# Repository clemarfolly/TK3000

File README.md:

# Microdigital TK-3000 IIe

A Microdigital Eletrônica Ltda foi uma das empresas pioneiras no mercado de microcomputadores no Brasil, tendo grande importância na popularização da informática durante a década de 1980. Fundada em 1979, a empresa se destacou por criar e distribuir uma série de microcomputadores compatíveis com modelos internacionais. A Microdigital se beneficiou da reserva de mercado imposta pelo governo brasileiro, o que levou a empresa a desenvolver produtos que atendessem à demanda interna por tecnologia, educação e entretenimento.

O TK-3000 IIe foi um computador pessoal brasileiro lançado em abril de 1986, inspirado no Apple IIe Enhanced, da Apple. Na época, ele chamou a atenção por oferecer boa compatibilidade com o sistema original, permitindo rodar diversos programas, jogos e ferramentas de programação. Equipado com processador de 1 MHz e 64 KB de memória RAM, o TK-3000 IIe também contava com recursos gráficos coloridos, teclado com acentuação em português e suporte a expansões e periféricos. Foi um dos computadores que marcaram a história da informática no Brasil durante os anos 1980, conquistando espaço entre usuários interessados em aprender programação, trabalhar e se divertir com a tecnologia da época.

## Sobre essa reprodução

A reprodução do projeto foi realizada sem acesso físico à placa original, com base em fotos da placa MA 104 sem componentes. Para isso, utilizou-se os software Sprint Layout e o KiCad para desenhar o esquema e a placa de circuito impresso. A réplica ainda não foi produzida, e seu funcionamento não foi validado. Agradecemos às pessoas que disponibilizaram as fotos e o esquema original, permitindo que esse trabalho fosse possível.

 ### Detalhes da placa
A placa é de dupla face e ficou com um tamanho final de 239 × 239 mm. Originalmente, os chips não têm uma identificação individual, sendo identificados apenas pela linha e coluna em que estão localizados. Para facilitar a montagem, adicionei o designador de cada circuito integrado diretamente na placa, dentro da área correspondente a ele.

### Comparação com a placa original
Como não tive acesso direto à placa original, fiz o que pude para que a recriação ficasse o mais fiel possível. Também recriei a fonte utilizada no projeto para deixar o resultado ainda mais parecido com o original.

O circuito de RF foi removido e, no lugar, foi adicionada uma saída de vídeo composto.

No TK-3000 original, a saída e a entrada de dados do cassete compartilham o mesmo circuito, o que pode causar incompatibilidades na leitura de dados a partir de algumas fontes de áudio. Para resolver esse problema, foi incluída uma entrada independente para leitura de dados, que pode ser ativada pelo jumper X6.

- Posição 1-2: mantém o funcionamento original do TK-3000.
- Posição 2-3: ativa a entrada independente de áudio para leitura de dados.

### Para confecção

Na seção de releases desta página, você encontrará todos os arquivos necessários para a fabricação da placa: o gerber em formato zip, o esquema em PDF e a lista interativa de materiais em HTML. Basta enviar o arquivo zip para a sua fabricante de PCB de preferência.

### Chips customizados

O TK-3000 possui três chips customizados: a MMU, a IOU e a GAL. Encontrar os chips originais MMU e IOU é bem difícil, mas é possível usar equivalentes do Apple IIe ou de clones asiáticos. Porém, é preciso ficar atento à disposição dos pinos, que pode ser diferente da original, exigindo o uso de adaptadores.

Outra alternativa mais moderna é utilizar versões desses chips recriadas em FPGA. Já a GAL é mais fácil de encontrar e está disponível para compra na internet.

As equações da GAL utilizadas no Apple IIe estão disponíveis na pasta PAL_G1 deste repositório e podem ser adaptadas para funcionar neste projeto.

## Créditos

### Recriação da Placa: 

Clemar Folly Jr.

https://x.com/clemarfolly/ - https://www.facebook.com/clemarjr

### Fotos 

Fotos da Placa sem componentes

William Barbacena, José Ferro

Post Facebook (indisponível no momento)

https://www.facebook.com/share/p/xtZCQikUJb32PADm/

Clube do TK - Logo Microdigital

http://www.tk90x.com.br/Download.html

Wikipedia

https://pt.wikipedia.org/wiki/Ficheiro:Microdigital_TK3000IIe_MoBo_MA104.jpg

### Esquema

Tabalabs - Esquema do TK 3000 e Diagrama de blocos

http://www.tabalabs.com.br/apple/esquemas_microdigital/index.htm

Esquemateca Tabalabs - Esquema do CCE Exato IIe

http://www.tabalabs.com.br/esquemateca/

### ROMs 

Datassette - Eduardo Luccas

https://datassette.org/pt-br/softwares/apple/apple-ii/firmwares/br-brasil/tk3000-roms-8kb

### Outras contribuições

Carlos Milek - Inclusão de alguns resistores, capacitores e transistor

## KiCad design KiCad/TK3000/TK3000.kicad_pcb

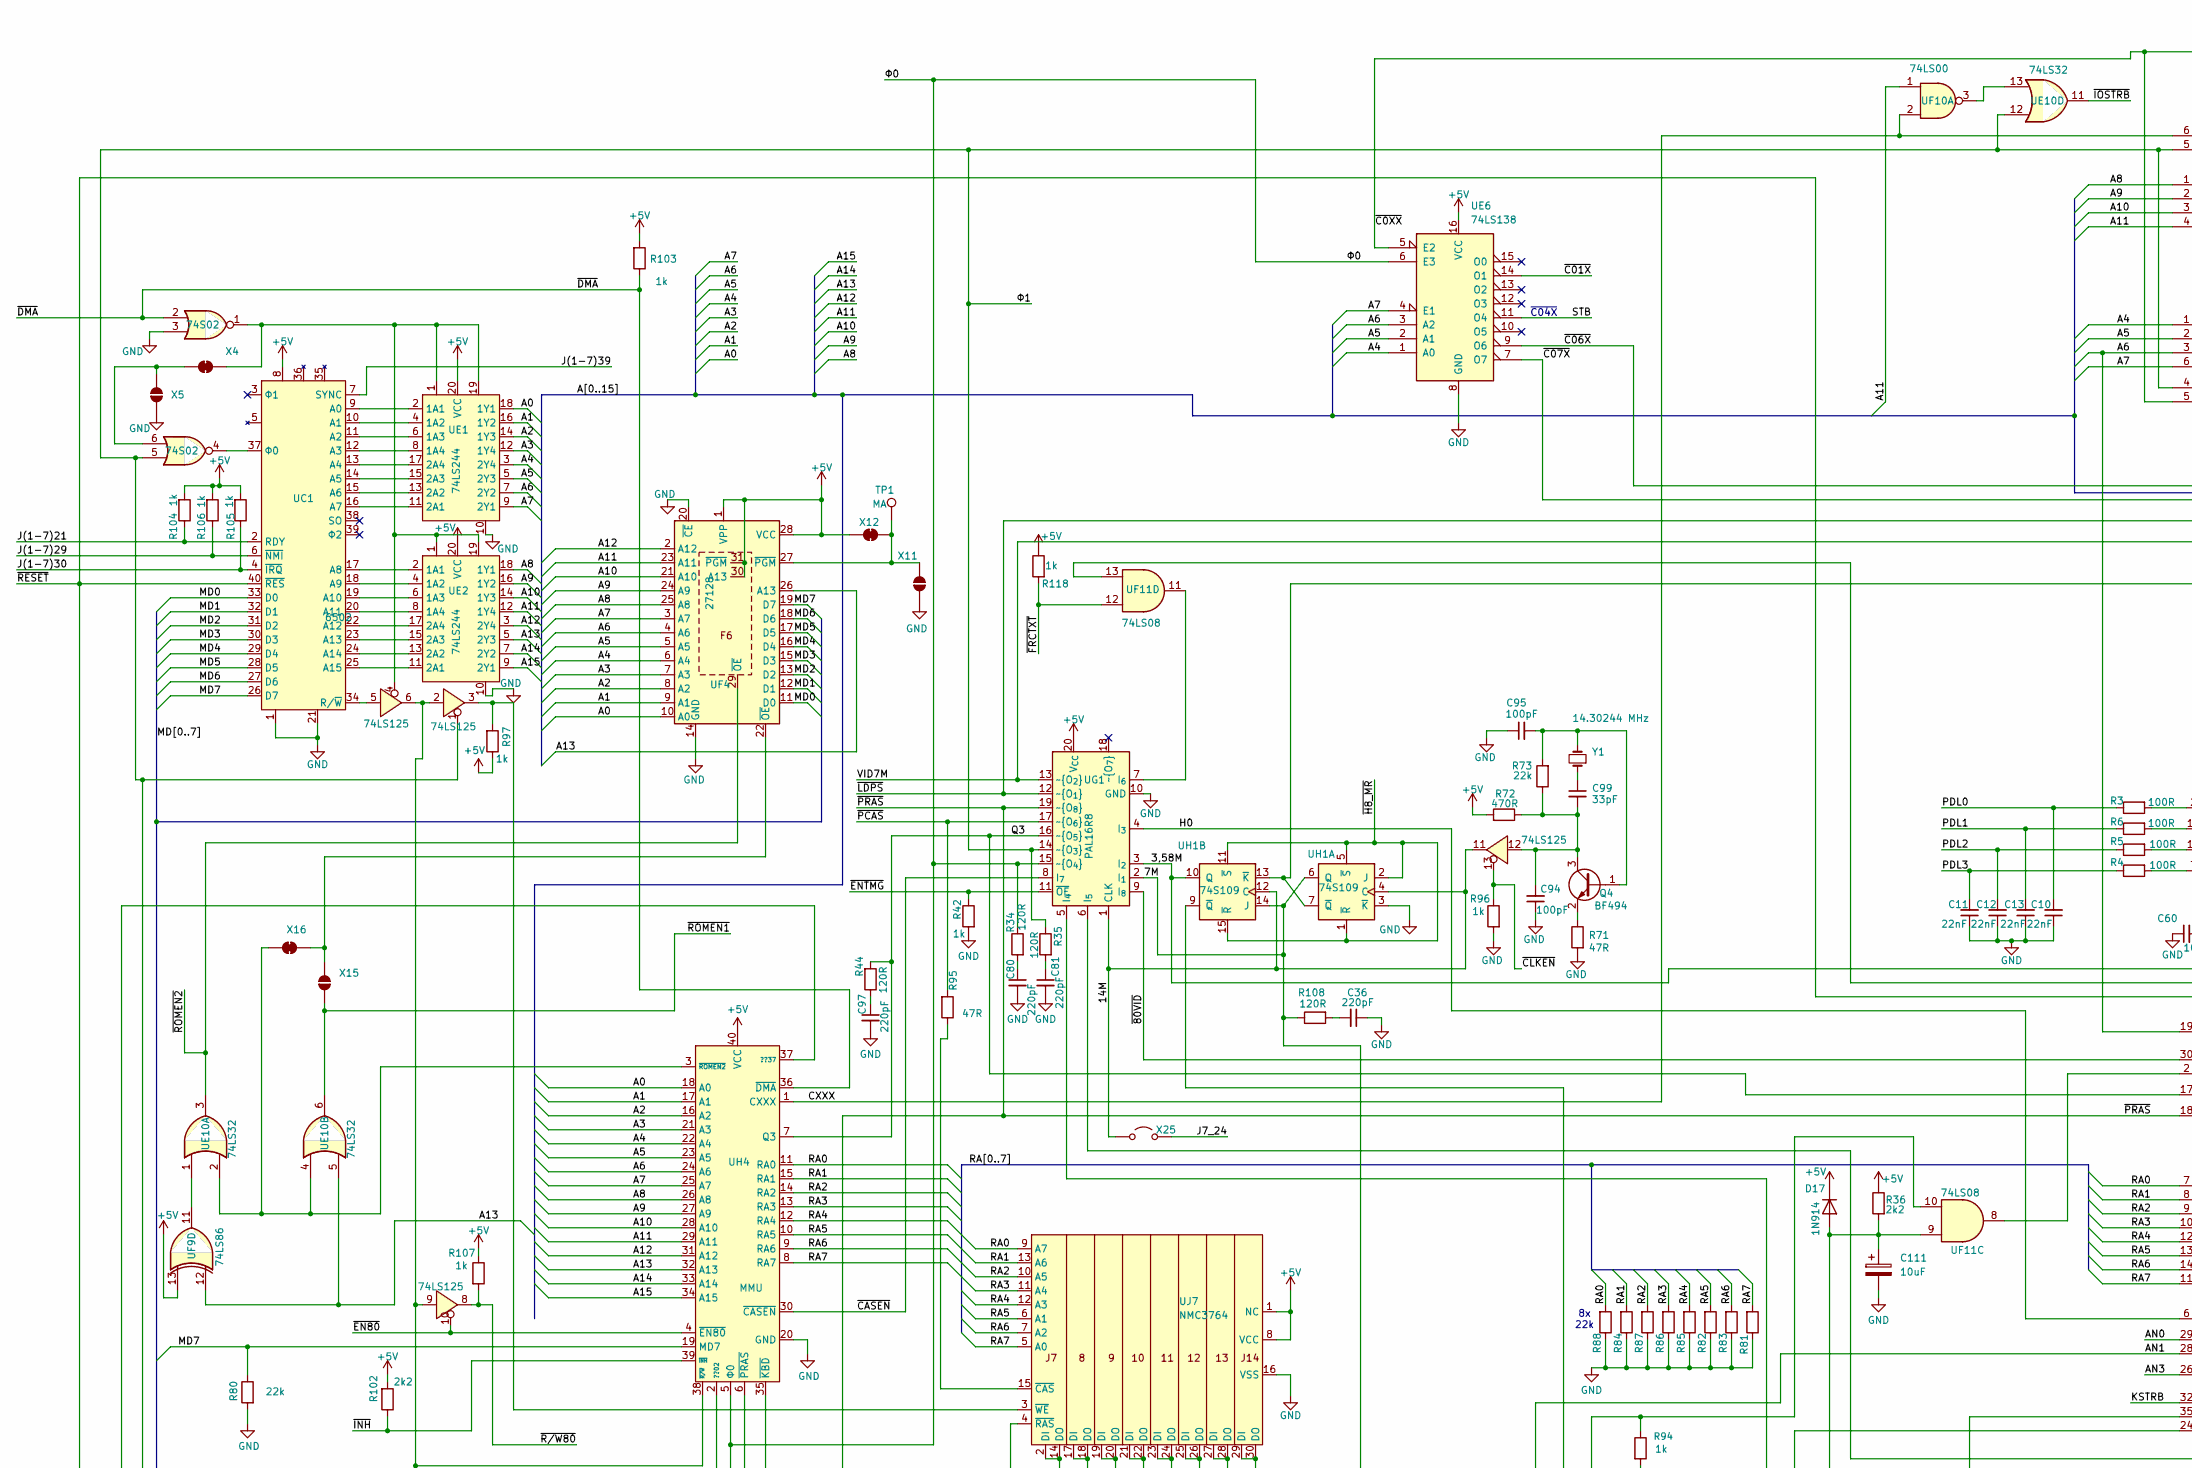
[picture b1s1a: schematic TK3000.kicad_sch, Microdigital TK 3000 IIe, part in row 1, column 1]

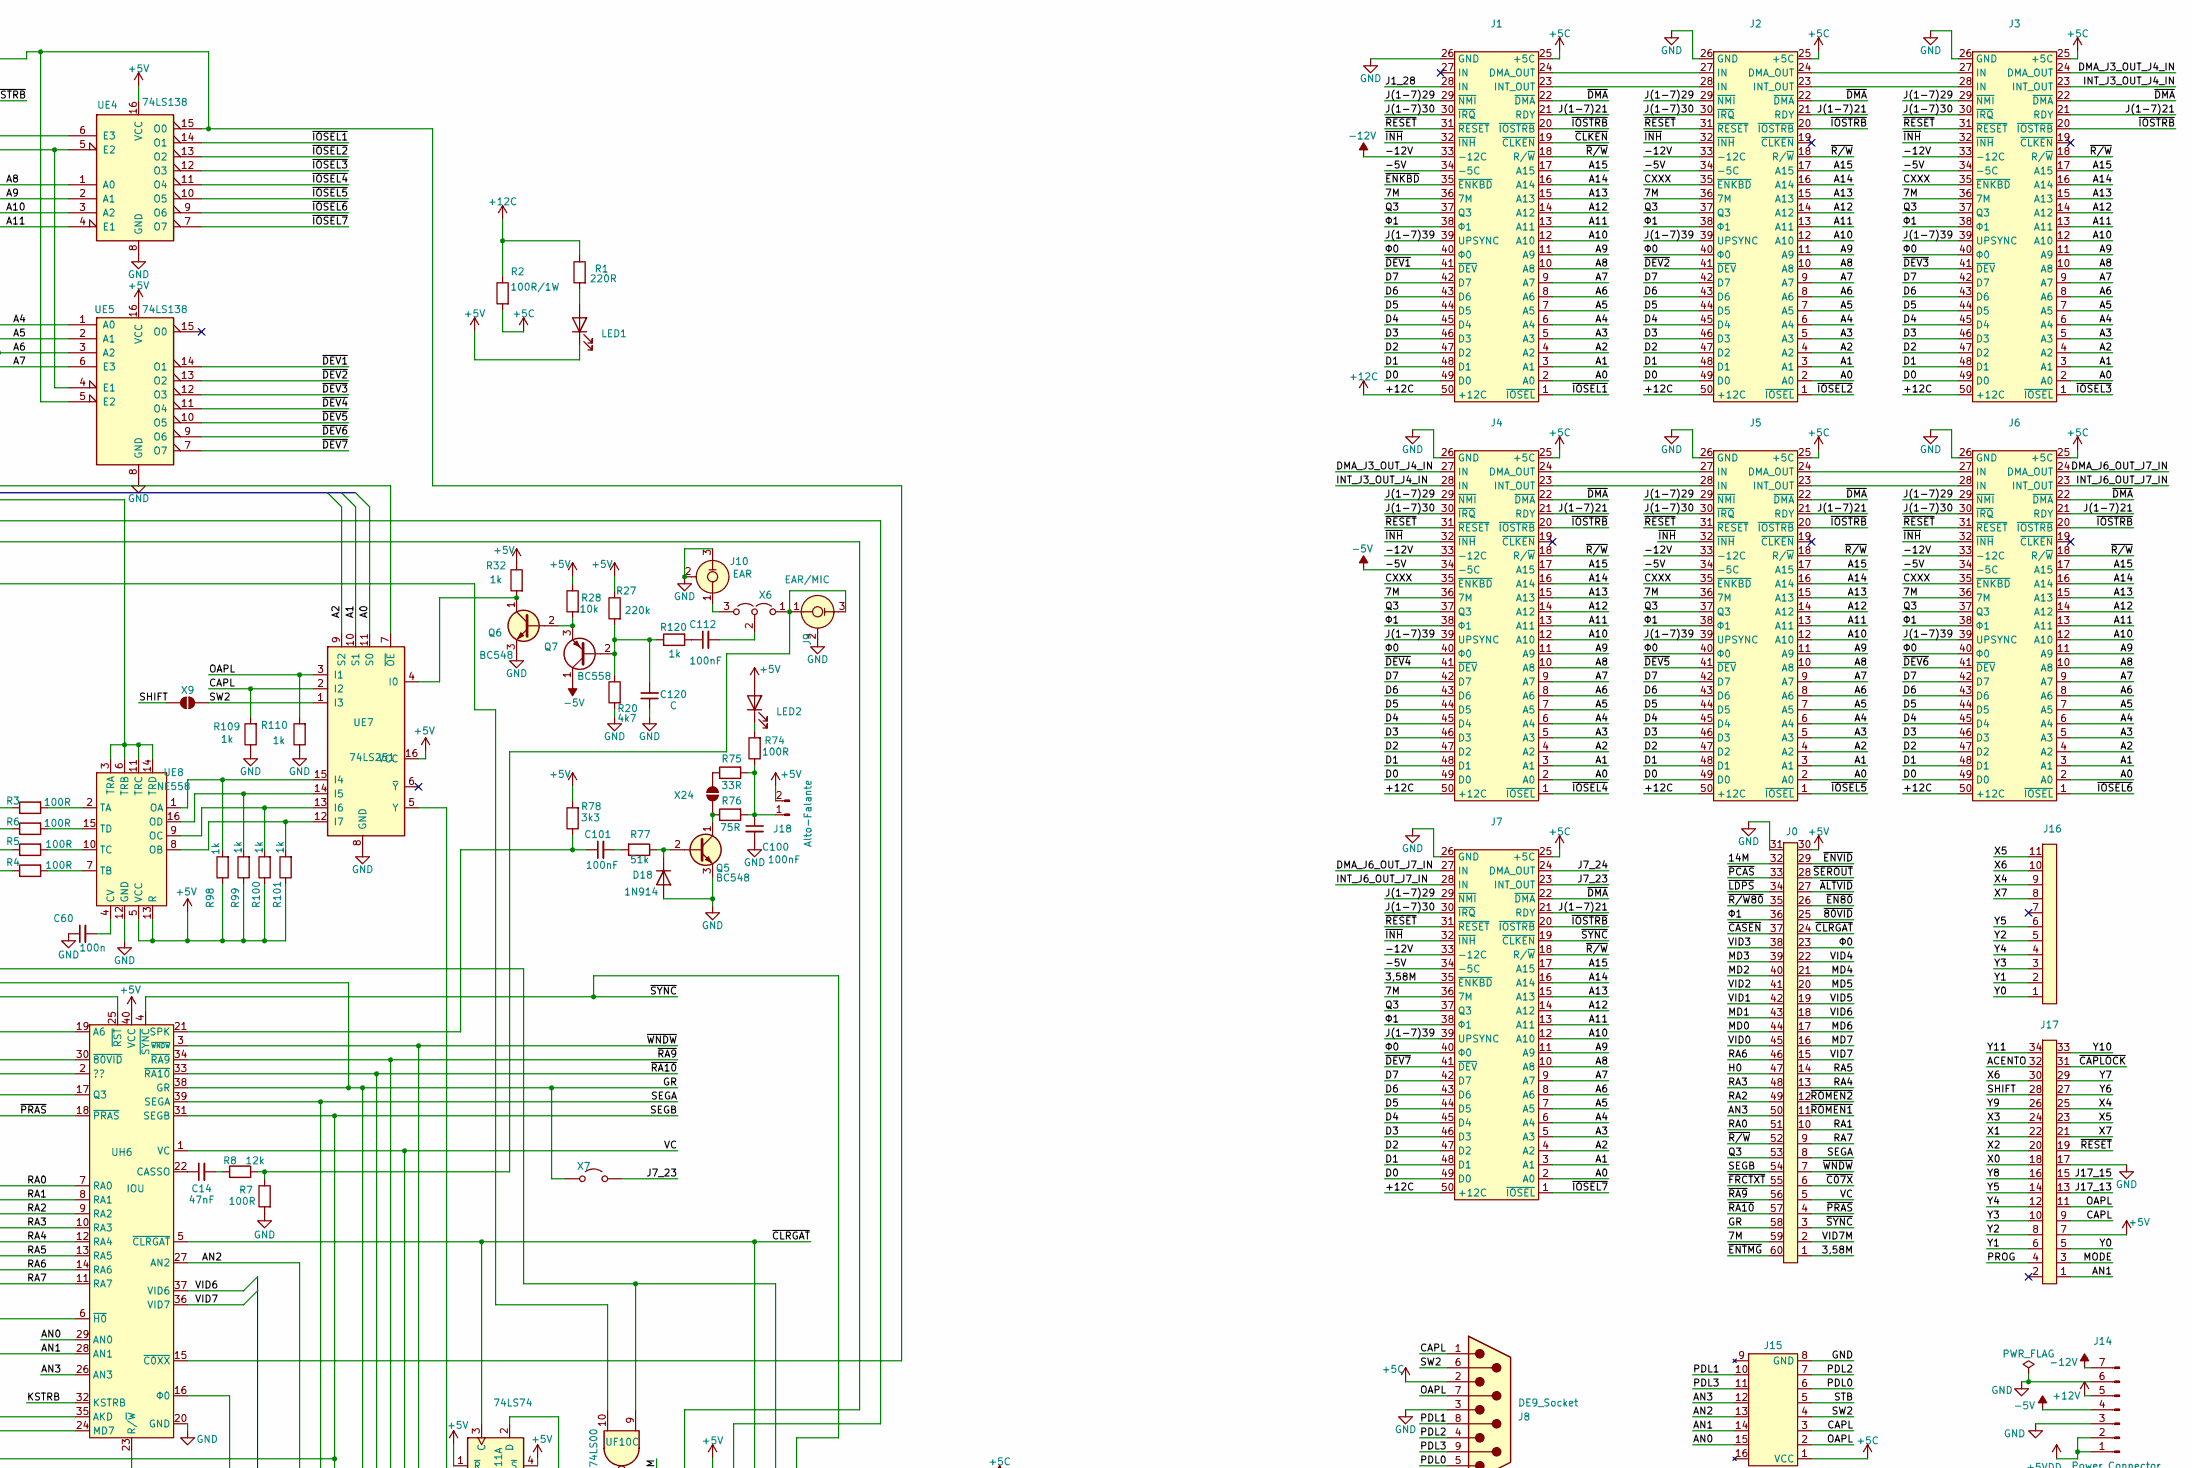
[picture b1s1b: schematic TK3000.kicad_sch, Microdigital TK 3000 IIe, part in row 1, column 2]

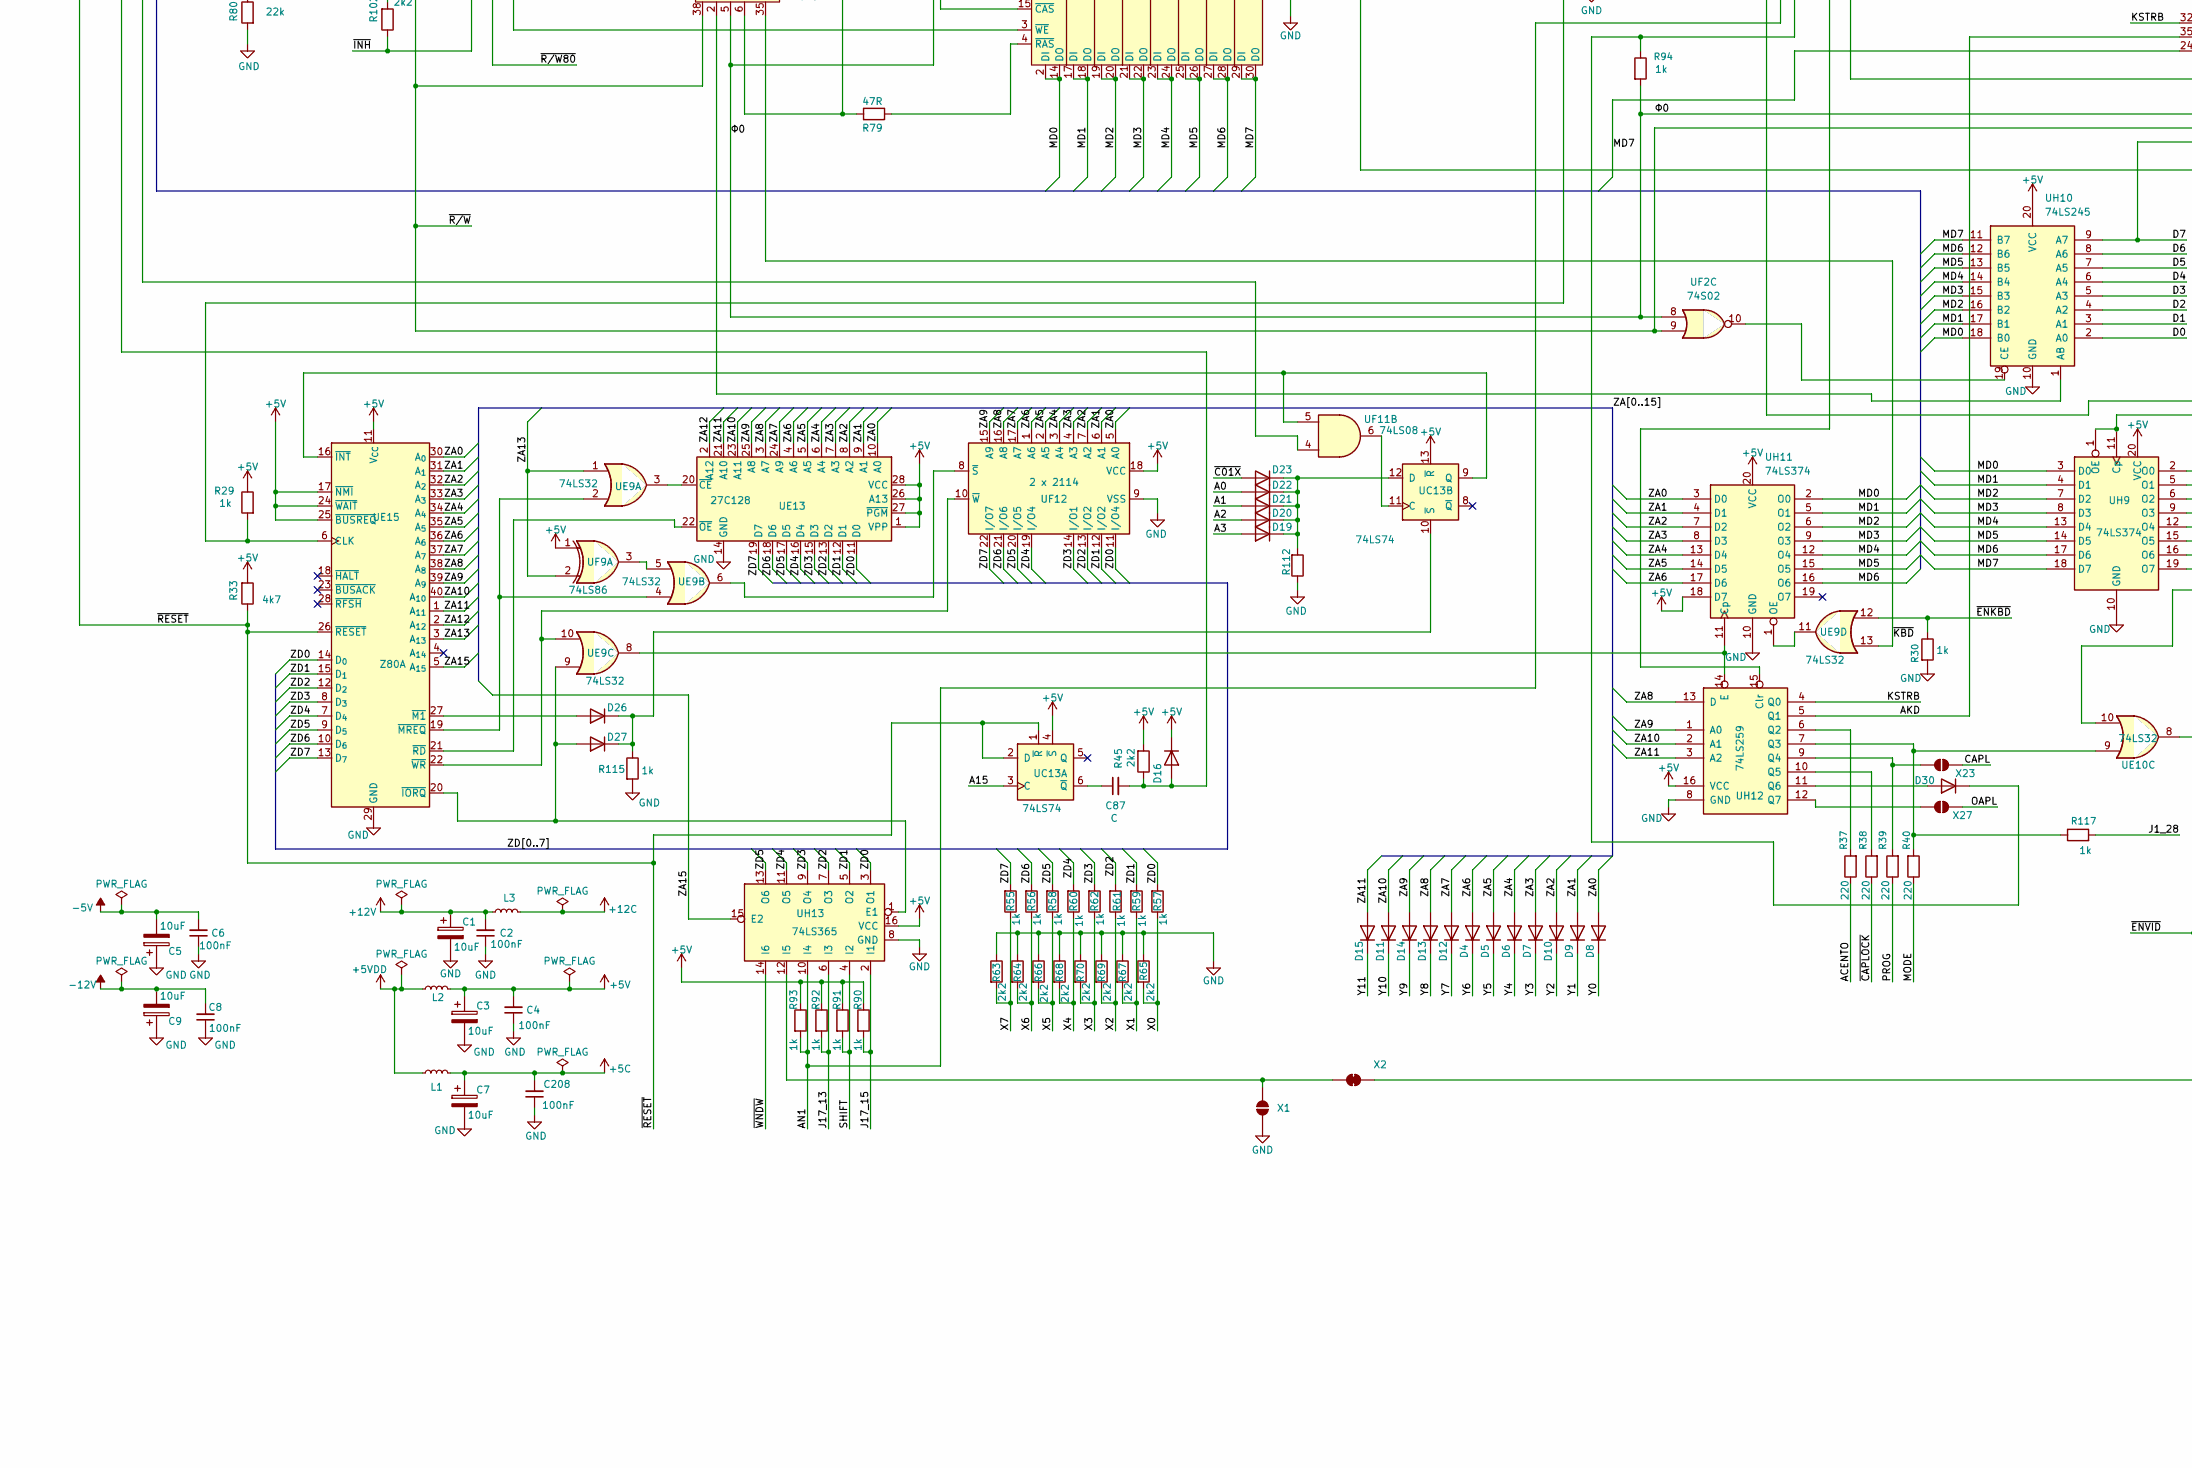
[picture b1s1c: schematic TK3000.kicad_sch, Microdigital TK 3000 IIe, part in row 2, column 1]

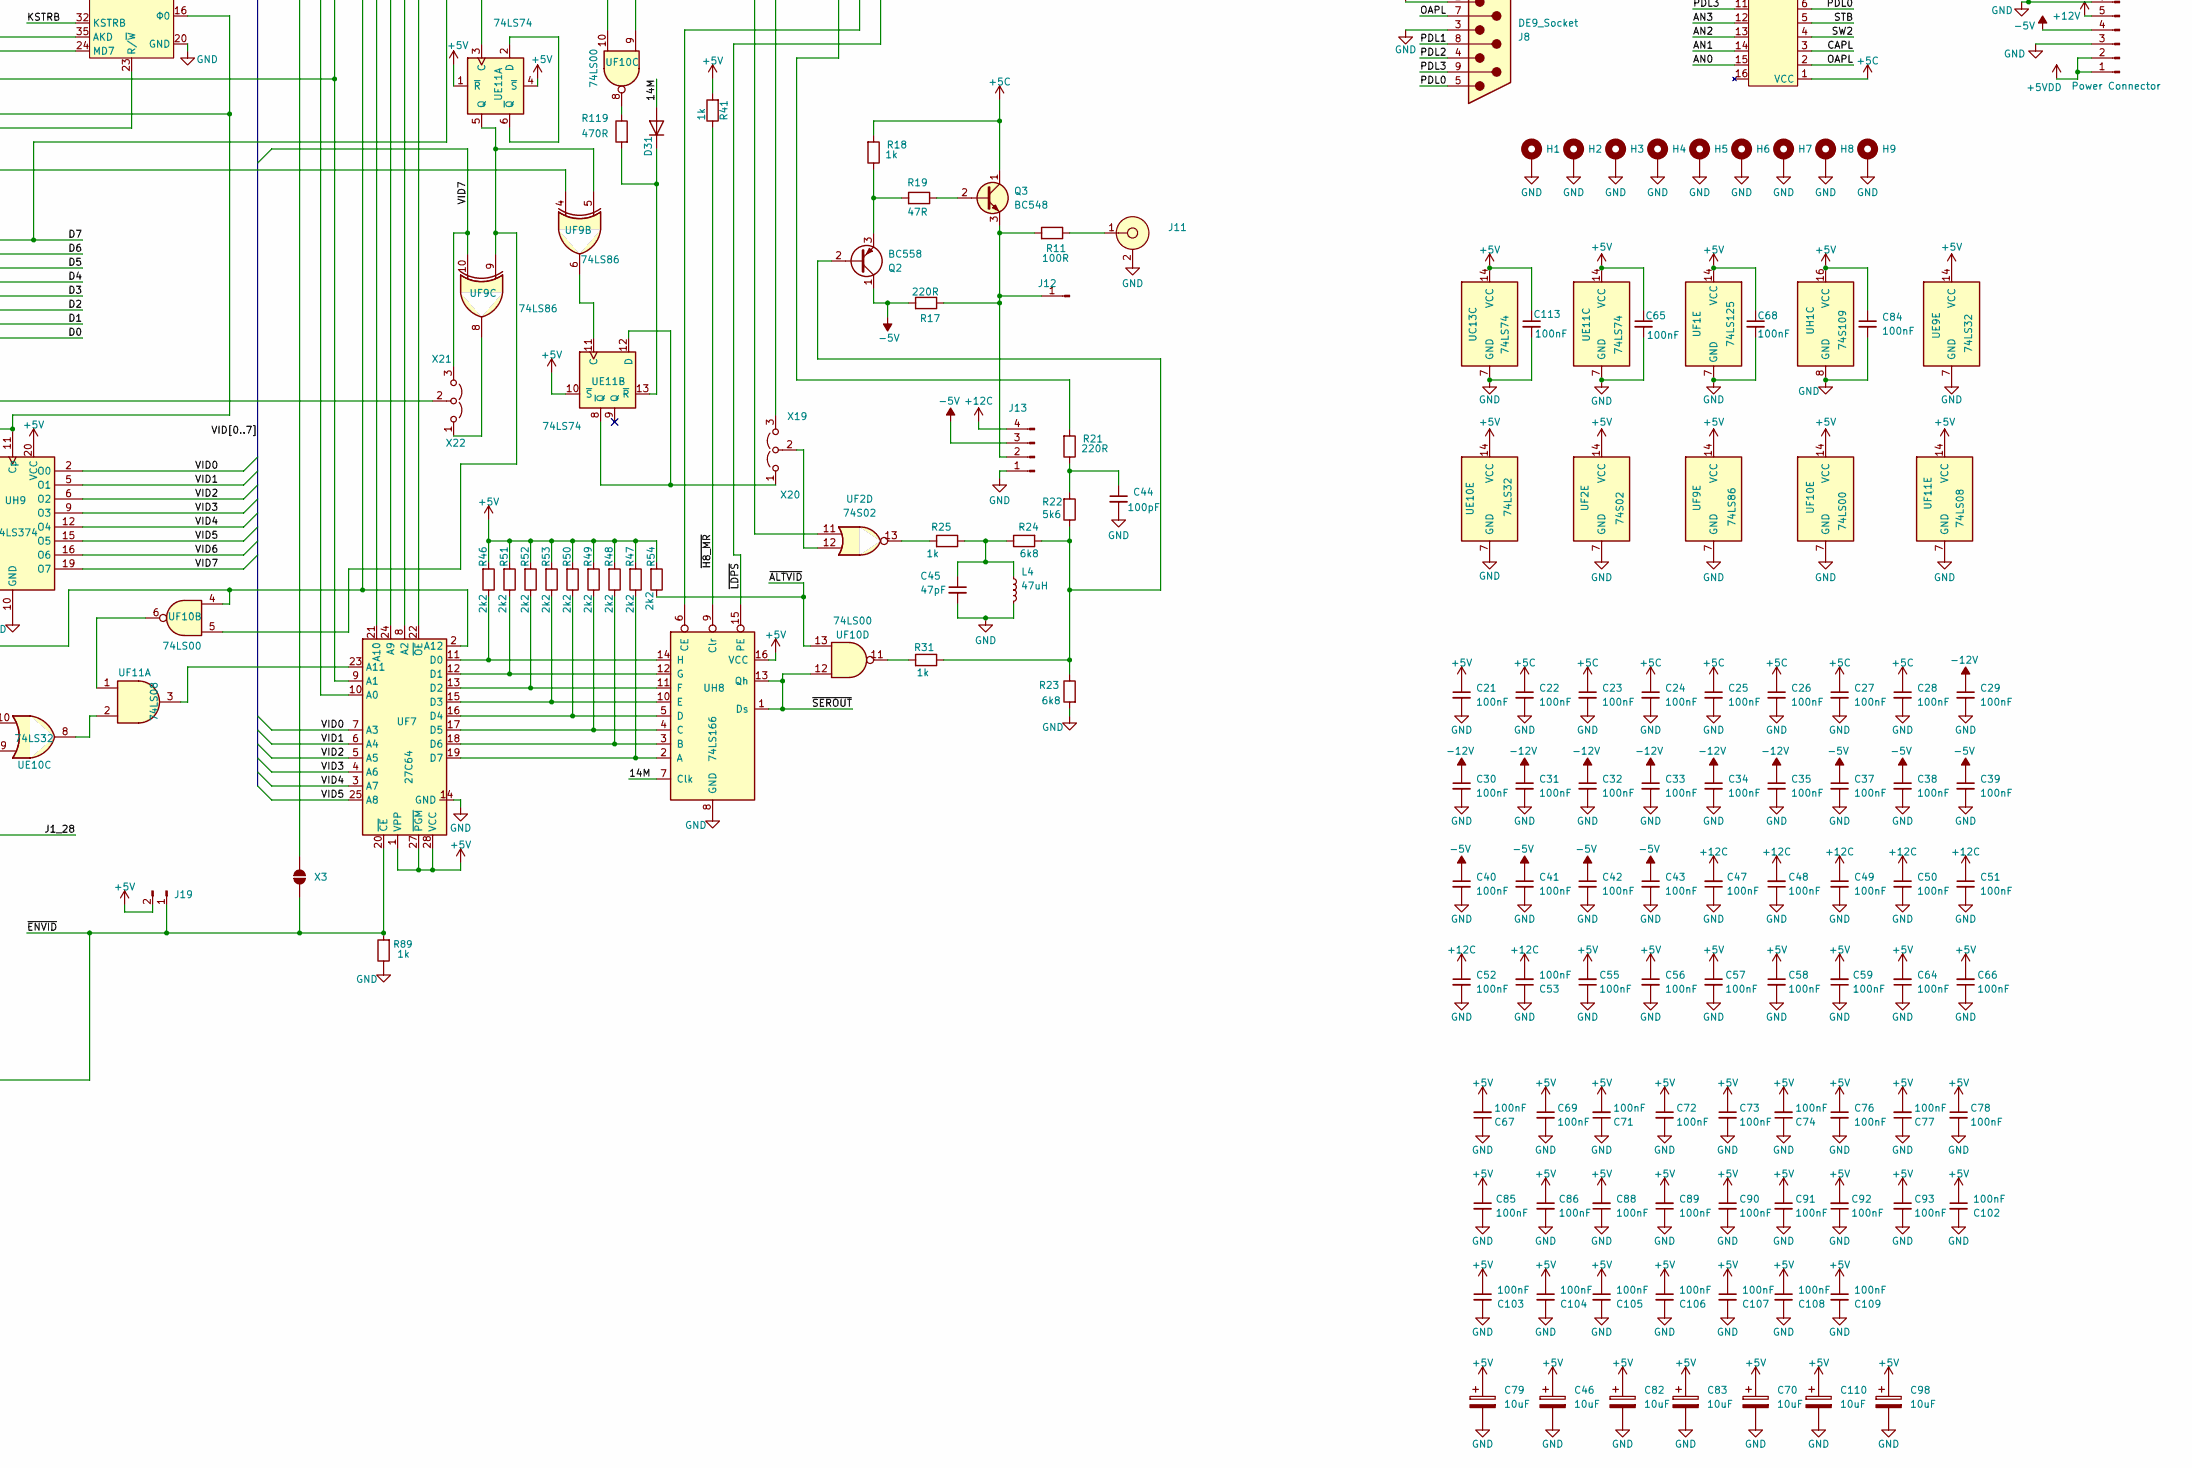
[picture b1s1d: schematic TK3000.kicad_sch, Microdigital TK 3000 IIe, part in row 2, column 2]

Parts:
C1, C3, C5, C9, C79, C82, C111: 10uF; C_Elet_111
C2, C4, C6, C8, C29, C30, C31, C32, C33, C34, C35, C57, C101, C112, C113, C208: 100nF; C_Disc_5.08
C7, C46, C70, C83: 10uF; C_Elet_Tipo2
C10, C11, C12, C13: 22nF; C_Disc_5.08
C14: 47nF; C_Disc_5.08
C21, C23, C24, C25, C26, C27, C28, C37, C38, C39, C40, C41, C42, C43, C47, C48, C49, C50, C51, C52, C53, C55, C58, C59, C64, C66, C67, C68, C69, C71, C72, C73, C74, C77, C78, C84, C86, C89, C90, C91, C92, C93, C102, C103, C104, C105, C106, C107, C108, C109: 100nF; C_Disc_5.08_12.7mm
C22, C56, C76, C85, C88: 100nF; C_Disc_12.7mm
C36, C80, C81, C97: 220pF; C_Disc_5.08
C44, C94, C95: 100pF; C_Disc_5.08
C45: 47pF; C_Disc_5.08
C60: 100n; C_Disc_5.08
C65: 100nF; C65_Disc_5.08_12.7mm
C87, C120: C; C_Disc_5.08
C98: 10uF; CP_Disc_5.08
C99: 33pF; C_Disc_5.08
C100: 100nF; C_Disc_C100
C110: 10uF; C_Elet_C110
D4, D5, D6, D7, D8, D9, D10, D11, D12, D13, D14, D15, D19, D20, D21, D22, D23, D30: 1N914; D_5.08
D16, D17, D26, D27, D31: 1N914; D_12.7
D18: 1N914; D_D18
H1, H9: MountingHole_Pad; Furo_8mm_5mm
H2, H3, H4: MountingHole_Pad; Furo_7mm_4mm
H5, H6, H7, H8: MountingHole_Pad; Furo_5mm_3mm
J0: SLOT-60_W5.08
J1, J2, J3, J4, J5, J6, J7: SLOT-50_W5.08
J8: DE9_Socket; DB9
J9: EAR/MIC; EarJack
J10: EAR; EarJack
J11: RCA_AV-8,4-5A
J12: Conn_01x01_Pin; J12
J13: J13
J14: Power Connector; J14
J15: GAME_IO
J16: J16
J17: J17
J18: Alto-Falante; J18
J19: Conn_01x02_Pin; PinHeader_1x02_P2.54mm_Vertical
L1, L2, L3: Ind
L4: 47uH; Ind_762
LED1: LED; led1
LED2: LED; led2
Q2, Q7: BC558
Q3, Q5, Q6: BC548
Q4: BF494
R1, R17, R21: 220R; Resistor_P12.70mm_Horizontal
R2: 100R/1W; Res_20.32
R3, R4, R5, R6, R7, R74: 100R; Resistor_P5.08mm_Vertical
R8: 12k; Resistor_P5.08mm_Vertical
R11: 100R; Resistor_P12.70mm_Horizontal
R18, R25, R29, R30, R31, R32, R89, R115, R117, R118, R120: 1k; Resistor_P12.70mm_Horizontal
R19: 47R; Resistor_P12.70mm_Horizontal
R20, R33: 4k7; Resistor_P12.70mm_Horizontal
R22: 5k6; Resistor_P12.70mm_Horizontal
R23, R24: 6k8; Resistor_P12.70mm_Horizontal
R27: 220k; Resistor_P12.70mm_Horizontal
R28: 10k; Resistor_P12.70mm_Horizontal
R34, R35, R44, R108: 120R; Resistor_P5.08mm_Vertical
R36, R45: 2k2; Resistor_P12.70mm_Horizontal
R37, R38, R39, R40: 220; Resistor_P5.08mm_Vertical
R41, R42, R55, R56, R57, R58, R59, R60, R61, R62, R90, R91, R92, R93, R94, R96, R97, R103, R104, R105, R106, R107, R109, R110, R112: 1k; Resistor_P5.08mm_Vertical
R46, R47, R48, R49, R50, R51, R52, R53, R54, R63, R64, R65, R66, R67, R68, R69, R70, R102: 2k2; Resistor_P5.08mm_Vertical
R71: 47R; Resistor_P2.54mm_Vertical
R72: 470R; Resistor_P2.54mm_Vertical
R73: 22k; Resistor_P2.54mm_Vertical
R75: 33R; Resistor_P5.08mm_Vertical
R76: 75R; Resistor_P2.54mm_Vertical
R77: 51k; Resistor_P2.54mm_Vertical
R78: 3k3; Resistor_P2.54mm_Vertical
R79, R95: 47R; Resistor_P5.08mm_Vertical
R80, R81, R82, R83, R84, R85, R86, R87, R88: 22k; Resistor_P5.08mm_Vertical
R98, R99, R100, R101: 1k; Resistor_P2.54mm_Vertical
R119: 470R; Resistor_P12.70mm_Horizontal
TP1: MA; TestPoint
UC1: 6502; DIP-40_W15.24mm
UC13: 74LS74; DIP-14_W7.62mm
UE1, UE2: 74LS244; DIP-20_W7.62mm
UE4: 74LS138; UE4_DIP-16_W7.62mm
UE5, UE6: 74LS138; DIP-16_W7.62mm
UE7: 74LS251; DIP-16_W7.62mm
UE8: NE558; DIP-16_W7.62mm
UE9: 74LS32; UE9_DIP-14_W7.62mm
UE10: 74LS32; UE10_DIP-14_W7.62mm
UE11: 74LS74; UE11_DIP-14_W7.62mm
UE13: 27C128; DIP-28_W15.24mm
UE15: Z80A; DIP-40_W15.24mm
UF1: 74LS125; DIP-14_W7.62mm
UF2: 74S02; DIP-14_W7.62mm
UF4: 27128; ROM_F4-F6
UF7: 27C64; UF7_DIP-28_W15.24mm
UF9: 74LS86; DIP-14_W7.62mm
UF10: 74LS00; DIP-14_W7.62mm
UF11: 74LS08; DIP-14_W7.62mm
UF12: 2 x 2114; RAM_F12-13
UG1: PAL16R8; UG1_DIP-20_W7.62mm
UH1: 74S109; DIP-16_W7.62mm
UH4: MMU; UH4_DIP-40_W15.24mm
UH6: IOU; UH6_DIP-40_W15.24mm
UH8: 74LS166; UH8_DIP-16_W7.62mm
UH9, UH11: 74LS374; DIP-20_W7.62mm
UH10: 74LS245; DIP-20_W7.62mm
UH12: 74LS259; DIP-16_W7.62mm
UH13: 74LS365; DIP-16_W7.62mm
UJ7: NMC3764; RAM_J7-J14
X1, X3, X5, X9, X15, X23, X27: SolderJumper_2_Open; Jumper_Aberto
X2, X4, X16: SolderJumper_2_Bridged; Jumper_Fechado
X6: PinHeader_1x03_P2.54mm_Vertical
X7, X25: Jumper_2_Open
X11: X11; Jumper_Aberto
X12: SolderJumper_2_Bridged; JP12
X19: X20; PinHeader_1x03_P2.54mm_Vertical
X21: X22; PinHeader_1x03_P2.54mm_Vertical
X24: SolderJumper_2_Open; X24
Y1: 14.30244 MHz; XTAL

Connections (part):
+5C: C7.1, C22.1, C23.1, C24.1, C25.1, C26.1, C27.1, C28.1, C208.2, J1.25 (+5C), J2.25 (+5C), J3.25 (+5C), J4.25 (+5C), J5.25 (+5C), J6.25 (+5C), J7.25 (+5C), J8.2, J15.1 (VCC), L1.2, Q3.1 (C), R2.1, R18.1
+5V: C3.1, C4.2, C21.1, C46.1, C55.2, C56.1, C57.1, C58.1, C59.2, C64.2, C65.1, C66.2, C67.2, C68.1, C69.1, C70.1, C71.2, C72.1, C73.1, C74.2, C76.1, C77.2, C78.1, C79.1, C82.1, C83.1, C84.1, C85.1, C86.1, C88.2, C89.2, C90.1, C91.1, C92.2, C93.1, C98.1, C102.1, C103.1, C104.1, C105.1, C106.1, C107.1, C108.1, C109.1, C110.1, C113.1, D16.1 (K), D17.1 (K), J0.30, J17.7, J18.2, J19.2, L2.2, LED1.1 (K), LED2.2 (A), R27.2, R28.2, R29.2, R32.2, R33.1, R36.2, R41.1, R45.1, R46.1, R47.1, R48.1, R49.1, R50.1, R51.1, R52.1, R53.1, R54.1, R72.1, R78.1, R90.2, R91.2, R92.2, R93.2, R97.2, R98.2, R99.2, R100.2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
+5VDD: J14.1, J14.2, L1.1, L2.1
+12C: C47.2, C48.2, C49.1, C50.1, C51.1, C52.1, C53.2, J1.50 (+12C), J2.50 (+12C), J3.50 (+12C), J4.50 (+12C), J5.50 (+12C), J6.50 (+12C), J7.50 (+12C), J13.4, L3.2, R1.2, R2.2
+12V: C1.1, C2.2, J14.5, L3.1
-5V: C5.2, C6.2, C37.1, C38.1, C39.1, C40.1, C41.1, C42.1, C43.1, J1.34 (-5C), J2.34 (-5C), J3.34 (-5C), J4.34 (-5C), J5.34 (-5C), J6.34 (-5C), J7.34 (-5C), J13.3, J14.4, Q2.1 (C), Q7.1 (C), R17.1
-12V: C8.2, C9.2, C29.1, C30.1, C31.1, C32.1, C33.1, C34.1, C35.1, J1.33 (-12C), J2.33 (-12C), J3.33 (-12C), J4.33 (-12C), J5.33 (-12C), J6.33 (-12C), J7.33 (-12C), J14.7
/3,58M: J0.1, J7.35 (~ENKBD), UF10.9, UG1.3 (I_{2}), UH1.10 (Q), X19.3 (B)
/7M: J0.59, J1.36 (7M), J2.36 (7M), J3.36 (7M), J4.36 (7M), J5.36 (7M), J6.36 (7M), J7.36 (7M), R108.2, UF9.4, UG1.2 (I_{1}), UH1.6 (Q), UH1.14 (J)
/14M: D31.2 (A), J0.32, UF1.11, UG1.1 (CLK), UH1.4 (C), UH1.12 (C), UH8.7 (Clk), X25.1 (A)
/A0: D22.2 (A), J1.2 (A0), J2.2 (A0), J3.2 (A0), J4.2 (A0), J5.2 (A0), J6.2 (A0), J7.2 (A0), UE1.18 (1Y1), UE7.11 (S0), UF4.10 (A0), UH4.18 (A0)
/A1: D21.2 (A), J1.3 (A1), J2.3 (A1), J3.3 (A1), J4.3 (A1), J5.3 (A1), J6.3 (A1), J7.3 (A1), UE1.16 (1Y2), UE7.10 (S1), UF4.9 (A1), UH4.17 (A1)
/A2: D20.2 (A), J1.4 (A2), J2.4 (A2), J3.4 (A2), J4.4 (A2), J5.4 (A2), J6.4 (A2), J7.4 (A2), UE1.14 (1Y3), UE7.9 (S2), UF4.8 (A2), UH4.16 (A2)
/A3: D19.2 (A), J1.5 (A3), J2.5 (A3), J3.5 (A3), J4.5 (A3), J5.5 (A3), J6.5 (A3), J7.5 (A3), UE1.12 (1Y4), UF4.7 (A3), UH4.21 (A3)
/A4: J1.6 (A4), J2.6 (A4), J3.6 (A4), J4.6 (A4), J5.6 (A4), J6.6 (A4), J7.6 (A4), UE1.3 (2Y4), UE5.1 (A0), UE6.1 (A0), UF4.6 (A4), UH4.22 (A4)
/A5: J1.7 (A5), J2.7 (A5), J3.7 (A5), J4.7 (A5), J5.7 (A5), J6.7 (A5), J7.7 (A5), UE1.5 (2Y3), UE5.2 (A1), UE6.2 (A1), UF4.5 (A5), UH4.23 (A5)
/A6: J1.8 (A6), J2.8 (A6), J3.8 (A6), J4.8 (A6), J5.8 (A6), J6.8 (A6), J7.8 (A6), UE1.7 (2Y2), UE5.3 (A2), UE6.3 (A2), UF4.4 (A6), UH4.24 (A6), UH6.19 (A6)
/A7: J1.9 (A7), J2.9 (A7), J3.9 (A7), J4.9 (A7), J5.9 (A7), J6.9 (A7), J7.9 (A7), UE1.9 (2Y1), UE5.6 (E3), UE6.4 (E1), UF4.3 (A7), UH4.25 (A7)
/A8: J1.10 (A8), J2.10 (A8), J3.10 (A8), J4.10 (A8), J5.10 (A8), J6.10 (A8), J7.10 (A8), UE2.18 (1Y1), UE4.1 (A0), UF4.25 (A8), UH4.26 (A8)
/A9: J1.11 (A9), J2.11 (A9), J3.11 (A9), J4.11 (A9), J5.11 (A9), J6.11 (A9), J7.11 (A9), UE2.16 (1Y2), UE4.2 (A1), UF4.24 (A9), UH4.27 (A9)
/A10: J1.12 (A10), J2.12 (A10), J3.12 (A10), J4.12 (A10), J5.12 (A10), J6.12 (A10), J7.12 (A10), UE2.14 (1Y3), UE4.3 (A2), UF4.21 (A10), UH4.28 (A10)
/A11: J1.13 (A11), J2.13 (A11), J3.13 (A11), J4.13 (A11), J5.13 (A11), J6.13 (A11), J7.13 (A11), UE2.12 (1Y4), UE4.4 (E1), UF4.23 (A11), UF10.1, UH4.29 (A11)
/A12: J1.14 (A12), J2.14 (A12), J3.14 (A12), J4.14 (A12), J5.14 (A12), J6.14 (A12), J7.14 (A12), UE2.3 (2Y4), UF4.2 (A12), UH4.31 (A12)
/A13: J1.15 (A13), J2.15 (A13), J3.15 (A13), J4.15 (A13), J5.15 (A13), J6.15 (A13), J7.15 (A13), UE2.5 (2Y3), UE10.5, UF4.26 (A13), UF9.12, UH4.32 (A13)
/A14: J1.16 (A14), J2.16 (A14), J3.16 (A14), J4.16 (A14), J5.16 (A14), J6.16 (A14), J7.16 (A14), UE2.7 (2Y2), UH4.33 (A14)
/A15: J1.17 (A15), J2.17 (A15), J3.17 (A15), J4.17 (A15), J5.17 (A15), J6.17 (A15), J7.17 (A15), UC13.3 (C), UE2.9 (2Y1), UH4.34 (A15)
/ACENTO: J17.32, R37.2
/AKD: UH6.35 (AKD), UH12.5 (Q1)
/AN0: J15.15, UH6.29 (AN0)
/AN1: J15.14, J17.1, R93.1, UH6.28 (AN1), UH13.10 (I4)
/AN2: J15.13, UH6.27 (AN2), X3.2 (B)
/AN3: J0.50, J15.12, UH6.26 (AN3)
/CAPL: J8.1, J15.3, J17.9, R109.1, UE7.2 (I2), X23.2 (B)
/CXXX: J2.35 (~ENKBD), J3.35 (~ENKBD), J4.35 (~ENKBD), J5.35 (~ENKBD), J6.35 (~ENKBD), UE4.6 (E3), UF10.2, UH4.1 (CXXX)
/D0: J1.49 (D0), J2.49 (D0), J3.49 (D0), J4.49 (D0), J5.49 (D0), J6.49 (D0), J7.49 (D0), UH10.2 (A0)
/D1: J1.48 (D1), J2.48 (D1), J3.48 (D1), J4.48 (D1), J5.48 (D1), J6.48 (D1), J7.48 (D1), UH10.3 (A1)
/D2: J1.47 (D2), J2.47 (D2), J3.47 (D2), J4.47 (D2), J5.47 (D2), J6.47 (D2), J7.47 (D2), UH10.4 (A2)
/D3: J1.46 (D3), J2.46 (D3), J3.46 (D3), J4.46 (D3), J5.46 (D3), J6.46 (D3), J7.46 (D3), UH10.5 (A3)
/D4: J1.45 (D4), J2.45 (D4), J3.45 (D4), J4.45 (D4), J5.45 (D4), J6.45 (D4), J7.45 (D4), UH10.6 (A4)
/D5: J1.44 (D5), J2.44 (D5), J3.44 (D5), J4.44 (D5), J5.44 (D5), J6.44 (D5), J7.44 (D5), UH10.7 (A5)
/D6: J1.43 (D6), J2.43 (D6), J3.43 (D6), J4.43 (D6), J5.43 (D6), J6.43 (D6), J7.43 (D6), UH10.8 (A6)
/D7: J1.42 (D7), J2.42 (D7), J3.42 (D7), J4.42 (D7), J5.42 (D7), J6.42 (D7), J7.42 (D7), UE7.5 (Y), UH10.9 (A7)
/DMA_J3_OUT_J4_IN: J3.24 (DMA_OUT), J4.27 (IN)
/DMA_J6_OUT_J7_IN: J6.24 (DMA_OUT), J7.27 (IN)
/GR: J0.58, UE10.10, UF7.2 (A12), UF10.4, UF11.13, UH6.38 (GR), X7.1 (A)
/H0: J0.47, UG1.4 (I_{3}), UH6.6 (~H0)
/INT_J3_OUT_J4_IN: J3.23 (INT_OUT), J4.28 (IN)
/INT_J6_OUT_J7_IN: J6.23 (INT_OUT), J7.28 (IN)
/J1_28: J1.28 (IN), R117.1
/J7_23: J7.23 (INT_OUT), X7.2 (B)
/J7_24: J7.24 (DMA_OUT), X25.2 (B)
/J17_13: J17.13, R92.1, UH13.6 (I3)
/J17_15: J17.15, R90.1, UH13.2 (I1)
/J(1-7)21: J1.21 (RDY), J2.21 (RDY), J3.21 (RDY), J4.21 (RDY), J5.21 (RDY), J6.21 (RDY), J7.21 (RDY), R104.2, UC1.2 (RDY)
/J(1-7)29: J1.29 (~NMI), J2.29 (~NMI), J3.29 (~NMI), J4.29 (~NMI), J5.29 (~NMI), J6.29 (~NMI), J7.29 (~NMI), R106.2, UC1.6 (~NMI)
/J(1-7)30: J1.30 (~IRQ), J2.30 (~IRQ), J3.30 (~IRQ), J4.30 (~IRQ), J5.30 (~IRQ), J6.30 (~IRQ), J7.30 (~IRQ), R105.2, UC1.4 (~IRQ)
/J(1-7)39: J1.39 (UPSYNC), J2.39 (UPSYNC), J3.39 (UPSYNC), J4.39 (UPSYNC), J5.39 (UPSYNC), J6.39 (UPSYNC), J7.39 (UPSYNC), UC1.7 (SYNC)
/KSTRB: UH6.32 (KSTRB), UH12.4 (Q0)
/MD0: J0.44, UC1.33 (D0), UF4.11 (D0), UH9.3 (D0), UH10.18 (B0), UH11.2 (O0), UJ7.2 (DI), UJ7.14 (DO)
/MD1: J0.43, UC1.32 (D1), UF4.12 (D1), UH9.4 (D1), UH10.17 (B1), UH11.5 (O1), UJ7.17 (DI), UJ7.18 (DO)
/MD2: J0.40, UC1.31 (D2), UF4.13 (D2), UH9.7 (D2), UH10.16 (B2), UH11.6 (O2), UJ7.19 (DI), UJ7.20 (DO)
/MD3: J0.39, UC1.30 (D3), UF4.15 (D3), UH9.8 (D3), UH10.15 (B3), UH11.9 (O3), UJ7.21 (DI), UJ7.22 (DO)
/MD4: J0.21, UC1.29 (D4), UF4.16 (D4), UH9.13 (D4), UH10.14 (B4), UH11.12 (O4), UJ7.23 (DI), UJ7.24 (DO)
/MD5: J0.20, UC1.28 (D5), UF4.17 (D5), UH9.14 (D5), UH10.13 (B5), UH11.15 (O5), UJ7.25 (DI), UJ7.26 (DO)
/MD6: J0.17, UC1.27 (D6), UF4.18 (D6), UH9.17 (D6), UH10.12 (B6), UH11.16 (O6), UJ7.27 (DI), UJ7.28 (DO)
/MD7: J0.16, R80.2, UC1.26 (D7), UF4.19 (D7), UH4.19 (MD7), UH6.24 (MD7), UH9.18 (D7), UH10.11 (B7), UJ7.29 (DI), UJ7.30 (DO)
/MODE: J17.3, R40.2
/OAPL: J8.7, J15.2, J17.11, R110.1, UE7.3 (I1), X27.2 (B)
/PDL0: C10.2, J8.5, J15.6, R3.2
/PDL1: C13.2, J8.8, J15.10, R6.2
/PDL2: C12.2, J8.4, J15.7, R5.2
/PDL3: C11.2, J8.9, J15.11, R4.2
/PROG: J17.4, R39.2
/Q3: J0.53, J1.37 (Q3), J2.37 (Q3), J3.37 (Q3), J4.37 (Q3), J5.37 (Q3), J6.37 (Q3), J7.37 (Q3), R44.1, UG1.16 (~O_{5}), UH4.7 (Q3), UH6.17 (Q3)
/RA0: J0.51, R88.1, UH4.11 (RA0), UH6.7 (RA0), UJ7.9 (A7)
/RA1: J0.10, R84.1, UH4.15 (RA1), UH6.8 (RA1), UJ7.13 (A6)
/RA2: J0.49, R87.1, UH4.14 (RA2), UH6.9 (RA2), UJ7.10 (A5)
/RA3: J0.48, R86.1, UH4.13 (RA3), UH6.10 (RA3), UJ7.11 (A4)
/RA4: J0.13, R85.1, UH4.12 (RA4), UH6.12 (RA4), UJ7.12 (A3)
/RA5: J0.14, R82.1, UH4.10 (RA5), UH6.13 (RA5), UJ7.6 (A1)
/RA6: J0.46, R83.1, UH4.9 (RA6), UH6.14 (RA6), UJ7.7 (A2)
/RA7: J0.9, R81.1, UH4.8 (RA7), UH6.11 (RA7), UJ7.5 (A0)
/SEGA: J0.8, UF7.10 (A0), UH6.39 (SEGA)
/SEGB: J0.54, UF7.9 (A1), UG1.6 (I_{5}), UH6.31 (SEGB)
/SHIFT: J17.28, R91.1, UH13.4 (I2), X9.1 (A)
/STB: J15.5, UE6.11 (O4)
/SW2: J8.6, J15.4, UE7.1 (I3), X9.2 (B)
/VC: J0.5, UF7.8 (A2), UH6.1 (VC)
/VID0: J0.45, UF7.7 (A3), UH9.2 (O0)
/VID1: J0.42, UF7.6 (A4), UH9.5 (O1)
/VID2: J0.41, UF7.5 (A5), UH9.6 (O2)
/VID3: J0.38, UF7.4 (A6), UH9.9 (O3)
/VID4: J0.22, UF7.3 (A7), UH9.12 (O4)
/VID5: J0.19, UF7.25 (A8), UH9.15 (O5)
/VID6: J0.18, UH6.37 (VID6), UH9.16 (O6)
/VID7: J0.15, UF9.10, UH6.36 (VID7), UH9.19 (O7), X21.3 (B)
/VID7M: J0.2, UG1.13 (~O_{2}), UH8.6 (CE)
/X0: J17.18, R57.2, R65.1
/X1: J17.22, R59.2, R67.1
/X2: J17.20, R61.2, R69.1
/X3: J17.24, R62.2, R70.1
/X4: J16.9, J17.25, R60.2, R68.1
/X5: J16.11, J17.23, R58.2, R66.1
/X6: J16.10, J17.30, R56.2, R64.1
/X7: J16.8, J17.21, R55.2, R63.1
/Y0: D8.1 (K), J16.1, J17.5
/Y1: D9.1 (K), J16.2, J17.6
/Y2: D10.1 (K), J16.5, J17.8
/Y3: D7.1 (K), J16.3, J17.10
/Y4: D6.1 (K), J16.4, J17.12
/Y5: D5.1 (K), J16.6, J17.14
/Y6: D4.1 (K), J17.27
/Y7: D12.1 (K), J17.29
/Y8: D13.1 (K), J17.16
/Y9: D14.1 (K), J17.26
/Y10: D11.1 (K), J17.33
/Y11: D15.1 (K), J17.34
/ZA0: D8.2 (A), UE13.10 (A0), UE15.30 (A_{0}), UF12.5 (A0), UH11.3 (D0)
/ZA1: D9.2 (A), UE13.9 (A1), UE15.31 (A_{1}), UF12.6 (A1), UH11.4 (D1)
/ZA2: D10.2 (A), UE13.8 (A2), UE15.32 (A_{2}), UF12.7 (A2), UH11.7 (D2)
/ZA3: D7.2 (A), UE13.7 (A3), UE15.33 (A_{3}), UF12.4 (A3), UH11.8 (D3)
/ZA4: D6.2 (A), UE13.6 (A4), UE15.34 (A_{4}), UF12.3 (A4), UH11.13 (D4)
/ZA5: D5.2 (A), UE13.5 (A5), UE15.35 (A_{5}), UF12.2 (A5), UH11.14 (D5)
/ZA6: D4.2 (A), UE13.4 (A6), UE15.36 (A_{6}), UF12.1 (A6), UH11.17 (D6)
/ZA7: D12.2 (A), UE13.24 (A9), UE15.37 (A_{7}), UF12.17 (A7)
/ZA8: D13.2 (A), UE13.3 (A7), UE15.38 (A_{8}), UF12.16 (A8), UH12.13 (D)
/ZA9: D14.2 (A), UE13.25 (A8), UE15.39 (A_{9}), UF12.15 (A9), UH12.1 (A0)
/ZA10: D11.2 (A), UE13.23 (A11), UE15.40 (A_{10}), UH12.2 (A1)
/ZA11: D15.2 (A), UE13.21 (A10), UE15.1 (A_{11}), UH12.3 (A2)
/ZA12: UE13.2 (A12), UE15.2 (A_{12})
/ZA13: UE9.1, UE15.3 (A_{13}), UF9.2
/ZA15: UE15.5 (A_{15}), UH13.15 (E2)
/ZD0: R57.1, UE13.11 (D0), UE15.14 (D_{0}), UF12.11 (I/O4), UH13.3 (O1)
/ZD1: R59.1, UE13.12 (D1), UE15.15 (D_{1}), UF12.12 (I/O2), UH13.5 (O2)
/ZD2: R61.1, UE13.13 (D2), UE15.12 (D_{2}), UF12.13 (I/O2), UH13.7 (O3)
/ZD3: R62.1, UE13.15 (D3), UE15.8 (D_{3}), UF12.14 (I/O1), UH13.9 (O4)
/ZD4: R60.1, UE13.16 (D4), UE15.7 (D_{4}), UF12.19 (I/O4), UH13.11 (O5)
/ZD5: R58.1, UE13.17 (D5), UE15.9 (D_{5}), UF12.20 (I/O5), UH13.13 (O6)
/ZD6: R56.1, UE13.18 (D6), UE15.10 (D_{6}), UF12.21 (I/O6)
/ZD7: R55.1, UE13.19 (D7), UE15.13 (D_{7}), UF12.22 (I/O7)
/~80VID: J0.25, UG1.9 (I_{8}), UH6.30 (~80VID)
/~ALTVID: J0.27, R54.2, UF10.13
/~C0XX: UE4.15 (O0), UE5.5 (E2), UE6.5 (E2), UH6.15 (~C0XX)
/~C01X: D23.2 (A), UE6.14 (O1)
/~C06X: UE6.9 (O6), UE7.7 (~OE)
/~C07X: J0.6, UE6.7 (O7), UE8.3 (TRA), UE8.6 (TRB), UE8.11 (TRC), UE8.14 (TRD)
/~CAPLOCK: J17.31, R38.2
/~CASEN: J0.37, UG1.8 (I_{7}), UH4.30 (~CASEN)
/~CLKEN: J1.19 (~CLKEN), R96.2, UF1.13
/~CLRGAT: J0.24, UE11.3 (C), UF2.11, UH6.5 (~CLRGAT)
/~DEV1: J1.41 (~DEV), UE5.14 (O1)
/~DEV2: J2.41 (~DEV), UE5.13 (O2)
/~DEV3: J3.41 (~DEV), UE5.12 (O3)
/~DEV4: J4.41 (~DEV), UE5.11 (O4)
/~DEV5: J5.41 (~DEV), UE5.10 (O5)
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
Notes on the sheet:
8x 22k
~{C04X}
